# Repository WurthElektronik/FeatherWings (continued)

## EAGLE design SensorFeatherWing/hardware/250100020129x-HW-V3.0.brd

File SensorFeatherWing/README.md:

# Sensor FeatherWing

## Introduction

The Würth Elektronik eiSos [Sensor FeatherWing](https://www.we-online.de/katalog/en/SENSOR_FeatherWing) is a sensor development board fully compatible to the popular [Adafruit](https://www.adafruit.com/) [Feather line](https://www.adafruit.com/feather) of development boards. It consists of the following four sensors:

* [**WSEN-PADS**](https://www.we-online.de/katalog/de/WSEN-PADS) - Absolute pressure sensor [(2511020213301)](https://www.we-online.de/katalog/datasheet/2511020213301.pdf)
* [**WSEN-ITDS**](https://www.we-online.de/katalog/de/WSEN-ITDS) - 3-axis acceleration sensor [(2533020201601)](https://www.we-online.de/katalog/datasheet/2533020201601_valid_from_2020-12-14.pdf)
* [**WSEN-TIDS**](https://www.we-online.de/katalog/de/WSEN-TIDS) - Temperature sensor [(2521020222501)](https://www.we-online.de/katalog/datasheet/2521020222501.pdf)
* [**WSEN-HIDS**](https://www.we-online.de/katalog/de/WSEN-HIDS) - Humidity and temperature sensor [(2525020210002)](https://www.we-online.de/katalog/datasheet/2525020210002.pdf)

All four sensors are connected over the shared I<sup>2</sup>C bus and hence can be connected to any of the Feather microcontroller boards. The available [Arduino](https://www.arduino.cc/) (C/C++) drivers and examples (see [software folder](software)) make it easy to build a prototype to kick-start the application development.

The Sensor FeatherWing also has a [4-pin JST QWIIC®](https://www.sparkfun.com/products/16766) connector on-board. This enables easy connection to SparkFun's [QWIIC® ecosystem](https://www.sparkfun.com/qwiic) of development boards. Additionally, a **6 pin connector** enables the extension of the FeatherWing with a host of [**evaluation boards from Würth Elektronik eiSos**](https://www.we-online.de/catalog/de/wco/wireless-connectivity_1/eval_boards).

This repository contains the [Eagle](https://www.autodesk.com/products/eagle/overview) design files for the Sensor FeatherWing [PCB](hardware) as well as the [software](software) with quick start example.

For more information, please download the [Sensor FeatherWing user manual](docs/SensorFeatherWing.pdf). Feel free to check our [YouTube channel](https://www.youtube.com/user/WuerthElektronik/videos) for video tutorials, hands-ons and webinars relating to our products.

## Hardware

### Description

The Sensor FeatherWing consists of four sensors. This section provides details regarding the key features of these sensors.

### [**WSEN-PADS**](https://www.we-online.de/katalog/de/WSEN-PADS) [(2511020213301)](https://www.we-online.de/katalog/datasheet/2511020213301.pdf)

The WSEN-PADS is a MEMS based piezo-resistive absolute pressure sensor with an integrated ASIC and an embedded temperature sensor. The fully molded holed LGA package and low current consumption makes this sensor suitable for a range of applications including weather stations, barometers, altimeters and indoor navigation.

#### Key features

* Absolute pressure range : 26 to 126 kPa
* Output data rate : 1 to 200 Hz
* Pressure data resolution : 24-bits
* Current consumption : 4 μA
* Programmable pressure threshold and data-ready interrupt

Further details about this sensor can be found under [we-online.de/katalog/en/WSEN-PADS](https://www.we-online.de/katalog/en/WSEN-PADS).

### [**WSEN-ITDS**](https://www.we-online.de/katalog/de/WSEN-ITDS) [(2533020201601)](https://www.we-online.de/katalog/datasheet/2533020201601_valid_from_2020-12-14.pdf)

The WSEN-ITDS sensor is a 14-bit digital ultra-low-power and high-performance three-axis accelerometer with a digital output interface. Capability of detecting events like free fall, tap recognition, wake up, stationary/motion, activity/inactivity and 6D orientation make the sensor suitable for applications like vibration monitoring, tilt measurement, impact detection and many more.

#### Key features

* Selectable full scale : ±2g, ±4g, ±8g, ±16g,
* Bandwidth : 400 Hz
* Output data rate : Up to 1600 Hz
* Noise density : 90 μg / 
* Operating modes : High-performance, Low-power, Normal
* Current consumption : 16 μA (Low-power mode)

Further details about this sensor can be found under [we-online.de/katalog/en/WSEN-ITDS](https://www.we-online.de/katalog/en/WSEN-ITDS).

### [**WSEN-TIDS**](https://www.we-online.de/katalog/de/WSEN-TIDS) [(2521020222501)](https://www.we-online.de/katalog/datasheet/2521020222501.pdf)

The WSEN-TIDS is a high precision silicon-based digital temperature sensor with an integrated ASIC and a digital I<sup>2</sup>C interface. A compact UDFN package and fast thermal response make this sensor ideal for a range of applications like environmental monitoring, HVAC, PCB thermal monitoring, industrial control and many more.

#### Key features

* Temperature range : -40 to 125 °C
* Output data rate : 25 to 200 Hz
* Temperature data resolution : 16-bits
* Current consumption : 1.75 μA
* Programmable temperature threshold interrupt

Further details about this sensor can be found under [we-online.de/katalog/en/WSEN-TIDS](https://www.we-online.de/katalog/en/WSEN-TIDS).

### [**WSEN-HIDS**](https://www.we-online.de/katalog/de/WSEN-HIDS) [(2525020210002)](https://www.we-online.de/katalog/datasheet/2525020210002.pdf)

The WSEN-HIDS is a 16-bit ultra-low power and high-performance humidity sensor with a digital interface. The pre-calibrated sensor in a compact LGA package is suitable for a variety of applications including HVAC systems, white goods, building automation and air conditioning.

#### Key features

* Humidity range : 0 to 100 %rH
* Current consumption : 2.2 μA (In high repeatability mode)
* Resolution : 0.01 %rH
* Response time : 4 s
* Integrated temperature sensor
  
Further details about this sensor can be found under [we-online.de/katalog/en/WSEN-HIDS](https://www.we-online.de/katalog/en/WSEN-HIDS).

### Pinouts

#### Feather Connector
This is the standard set of connectors that is used across the Feather ecosystem. The table below describes the functions of each of the 28 pins as applicable to this FeatherWing.

| Pin number | Pin name | Function |
| ------- | ------- |----------------|
|   1          | <span style="text-decoration:overline">RST</span> | Not connected|
|    2          | 3V3| 3.3 V power supply|
|    3          | AREF| Not connected|
|    4          | GND| Ground|
|    5          | A0| Not connected|
|    6          | A1| Not connected|
|    7          | A2| Not connected|
|    8          | A3| Not connected|
|    9          | A4| Not connected|
|    10         | A5| (Optional) SPI_CE via JP1|
|    11         | SCK| SPI clock|
|    12         | MOSI| SPI MOSI|
|    13         | MISO| SPI MOSI|
|    14         | U0RX| Not connected|
|    15         | U0TX| Not connected|
|    16         | NC| Not connected|

| Pin number | Pin name | Function |
| ------- | ------- |----------------|
|    17         | SDA| I<sup>2</sup>C SDA|
|    18         | SCL|  I<sup>2</sup>C SCL|
|    19         | 5| Not connected|
|    20         | 6| Not connected|
|    21         | 9| Not connected|
|    22         | U1TX| Not connected|
|    23         | U1RX| Not connected|
|    24         | 12| Not connected|
|    25         | 13| Not connected|
|    26         | 5V| 5 V Power supply|
|    27         | EN| Not connected|
|    28         | VBAT| Not connected|

### Layout

#### Connector CON1
Connector CON1 is a 1x5 2.54 mm pin header and provides all the interrupt lines that can be optionally connected to the host. This connector is not mounted.

| Pin number  | Function |
| ------- | ------- |
|     1 |  Not used|
|     2|  Interrupt 1 of the WSEN-ITDS sensor|
|     3 | Interrupt 0 of the WSEN-ITDS sensor |
|     4 | Interrupt of the WSEN-PADS sensor|
|    5 | Interrupt of the WSEN-TIDS sensor| 

#### Connectors CON2 and CON3
CON2 (mounted) and CON3 (not mounted) are 4-pin JST connectors that allow interfacing with [SparkFun's QWIIC®](https://www.sparkfun.com/qwiic) development board ecosystem.
CON3 is not mounted and needs to be soldered on in order to be daisy chain-able. The QWIIC® ecosystem offers a wide range of development boards and accessories for quick prototyping.

| Pin number  | Function |
| ------- | ------- |
|    1 | I<sup>2</sup>C SCL |
|    2|  I<sup>2</sup>C SDA|
|    3 | VCC |
|    4 | GND|

#### Connector CON4
The connector 4 (not mounted) is a 2x3 2.54 mm pitch plug that is compatible with the [Sensor EV-boards](https://www.we-online.de/katalog/de/wco/sensors/evaluation_boards_wsen) from Würth Elektronik using the **SPI** interface.

| Pin number  | Function |
| ------- | ------- |
|    1 | GND|
|    2 | SPI_SCK (Clock) |
|    3|  SPI_MOSI (Master Out Slave In) |
|    4 | SPI_CE (Chip Enable) |
|    5|  SPI_MISO (Master In Slave Out)|
|   6|  VCC|

#### Connector CON5
The connector 5 is a 2x3 2.54 mm pitch plug that is compatible with the [Sensor EV-boards](https://www.we-online.de/katalog/de/wco/sensors/evaluation_boards_wsen) from Würth Elektronik using the **I<sup>2</sup>C** interface.

#### Jumper JP1
This jumper has to be mounted and set when CON4 is used to connect to a sensor using the **SPI** interface.
| Pin connection | Function  | Jumper set (Default) |
| ------- | ------- |----------------|
|    1,2	| SPI_CE(CON4) to GPIOA5 |	No (Not mounted)|

#### Jumper JP2
The standard I<sup>2</sup>C interface requires the SCL and SDA lines to be pulled up with resistors. These jumpers can be removed in cases where the pull-ups already exist on the I<sup>2</sup>C bus.
| Pin connection | Function  | Jumper set (Default) |
| ------- | ------- |----------------|
|    1,2|	Connect  I<sup>2</sup>C SCL line to a 4.7 k<span>&#8486;</span> Pull up resistor|	Yes|
|    3,4|	Connect  I<sup>2</sup>C SDA line to a 4.7 k<span>&#8486;</span> Pull up resistor|	Yes|

### Schematics

### DISCLAIMER:
THE USE OF THE WÜRTH ELEKTRONIK EISOS DESIGN EXAMPLE / REFERENCE DESIGN IS ENTIRELY AT YOUR OWN RISK. IT IS YOUR SOLE RESPONSIBILITY TO IMPLEMENT THE DESIGN EXAMPLE / REFERENCE DESIGN WITH ALL TECHNICAL AND REGULATORY REQUIREMENTS IN YOUR APPLICATION. IT IS ALSO YOUR RESPONSIBILITY TO VERIFY THE FUNCTION AND PERFORMANCE OF YOUR DESIGN IN YOUR OWN PARTICULAR ENGINEERING AND PRODUCT ENVIRONMENT AND YOU ASSUME THE ENTIRE RISK OF DOING SO OR FAILING TO DO SO. THE WÜRTH ELEKTRONIK EISOS DESIGN EXAMPLE / REFERENCE DESIGN IS PROVIDED ON AN "AS IS" OR "AS AVAILABLE" BASIS, WITHOUT ANY WARRANTIES OF ANY KIND AND WÜRTH ELEKTRONIK EISOS DISCLAIMS ANY WARRANTIES EXPRESS OR IMPLIED, INCLUDING WITHOUT LIMITATION THE MERCHANTABILITY OR FITNESS FOR A PARTICULAR PURPOSE, USAGE OR THE NON-INFRINGEMENT OF THIRD PARTIES’ INTELLECTUAL PROPERTY RIGHTS. NO LICENSE IS GRANTED TO ANY INTELLECTUAL PROPERTY RIGHT BY WÜRTH ELEKTRONIK EISOS OR ANY THIRD PARY. UNDER NO CIRCUMSTANCES SHALL WÜRTH ELEKTRONIK EISOS BE LIABLE FOR DAMAGES INCURRED BY REASON OF OTHER SERVICES OR PRODUCTS RECEIVED THROUGH OR ADVERTISED IN CONNECTION WITH THE WÜRTH ELEKTRONIK EISOS SITE OR THE WÜRTH ELEKTRONIK EISOS DESIGN EXAMPLE / REFERENCE DESIGN. THE WÜRTH ELEKTRONIK EISOS DESIGN EXAMPLE / REFERENCE DESIGN IS SUBJECT TO CHANGE WITHOUT NOTICE.

## Software

Sensor FeatherWing **software examples** can be found in the [software folder](software).

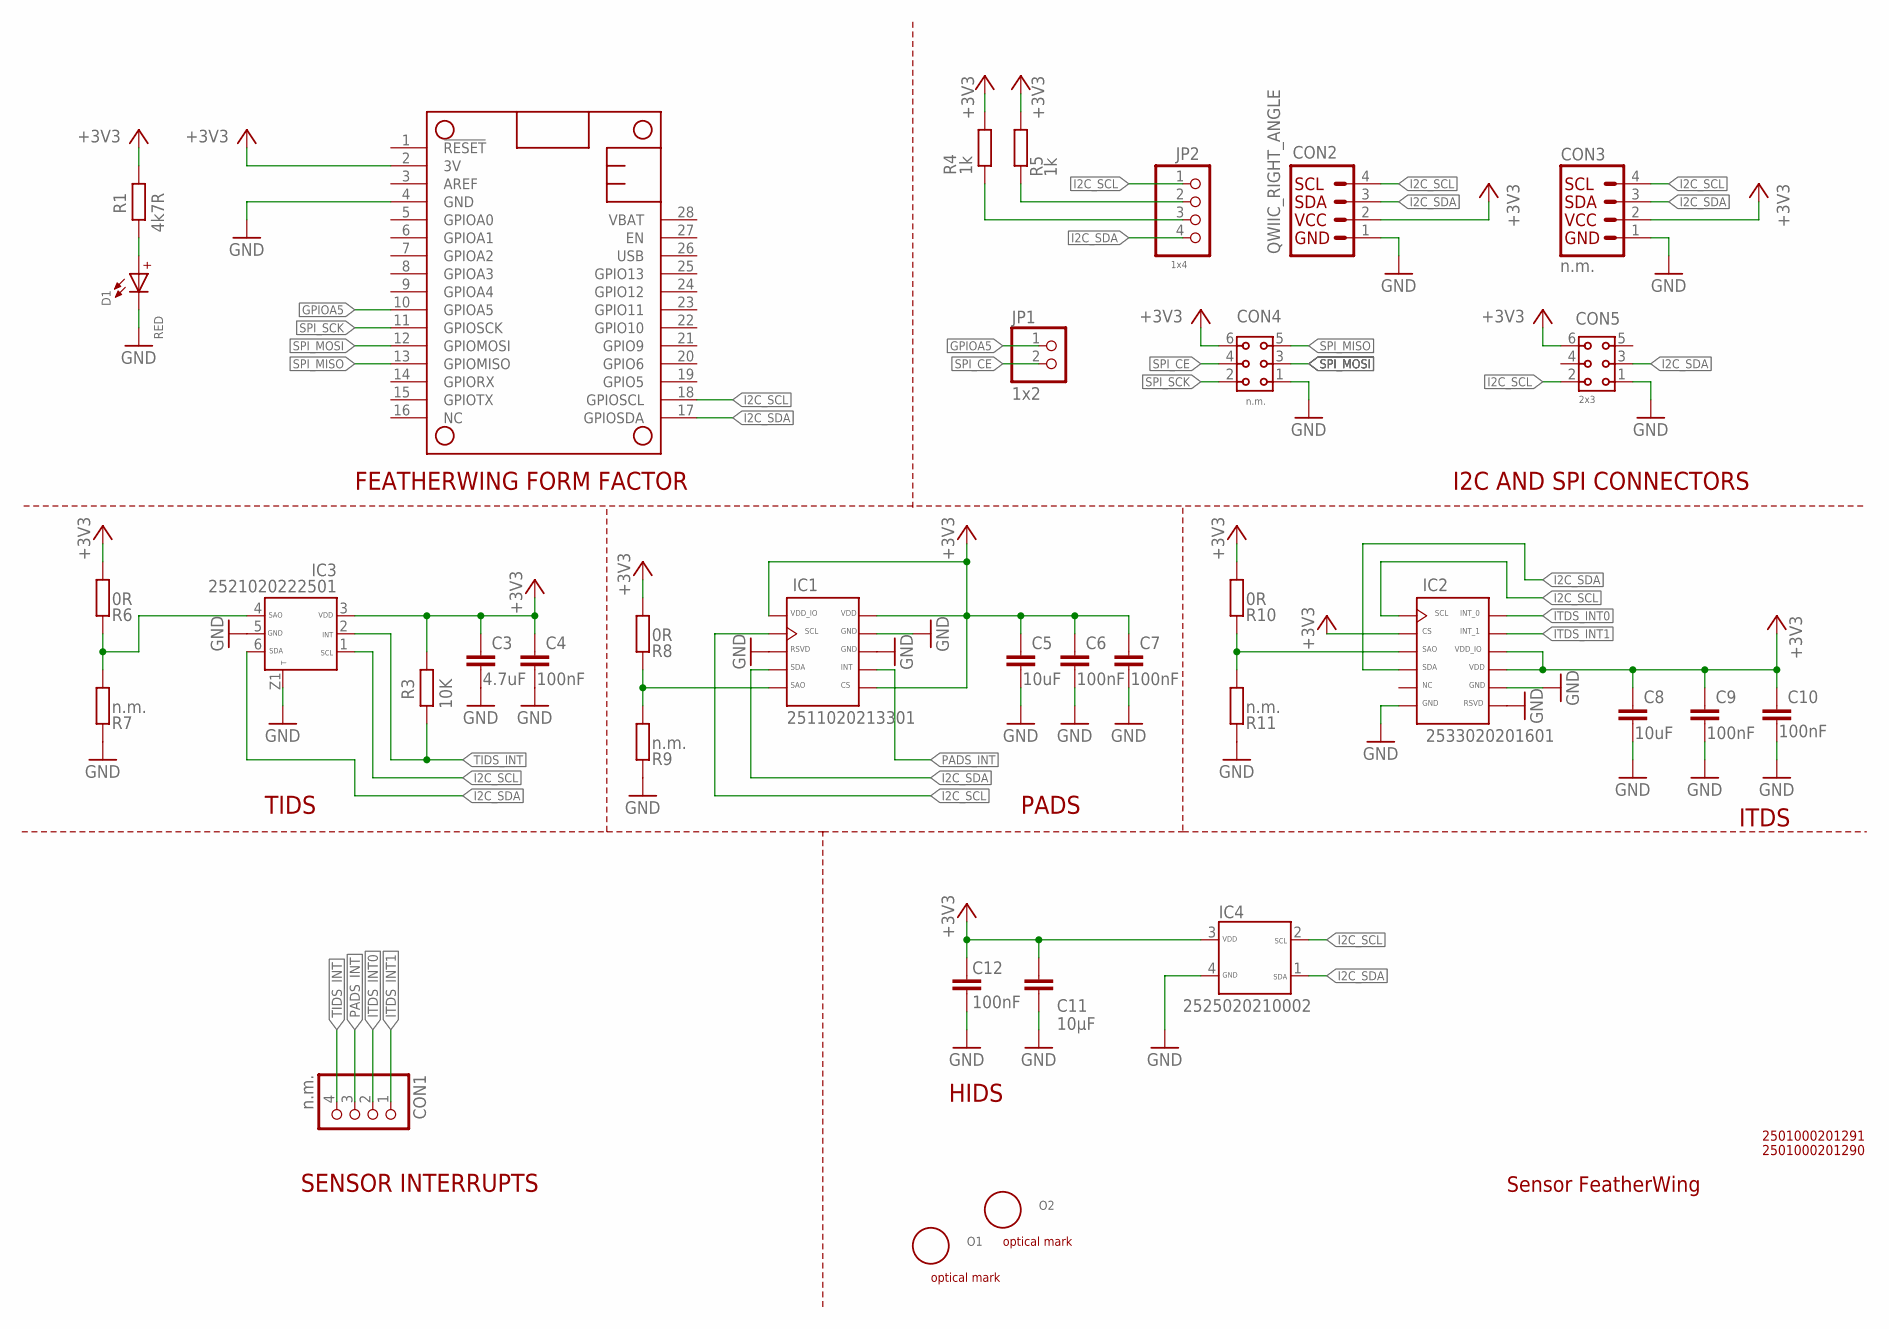
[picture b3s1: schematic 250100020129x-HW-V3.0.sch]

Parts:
C3: 4.7uF; C0402_IPC
C4, C6, C7, C9, C10, C12: 100nF; C0402_IPC
C5, C8: 10uF; C0402_IPC
C11: 10µF; C0402_IPC
CON1: n.m.; 1X04/R
CON2: QWIIC_RIGHT_ANGLE; JST04_1MM_RA
CON3: n.m.; JST04_1MM_RA
CON4: n.m.; 613006243121
CON5: 2x3; 613006243121
D1: RED; WL-SMSW_1204_A
IC1: 2511020213301; WSEN-PADS_2511020213301
IC2: 2533020201601; WSEN-ITDS_2533020201601
IC3: 2521020222501; WSEN-TIDS_2521020222501
IC4: 2525020210002; WSEN-HIDS_2525020210002
JP1: 1x2; 1X02/R
JP2: 1x4; 1X04/R
MS1: FEATHERWING
O1, O2: OPT_MARKE; OPTISCHE_MARKE
R1: 4k7R; R0402_IPC
R3: 10K; R0402_IPC
R4, R5: 1k; R0402_IPC
R6, R8, R10: 0R; R0402_IPC
R7, R9, R11: n.m.; R0402_IPC

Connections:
+3V3: C3.1, C4.1, C5.1, C6.1, C7.1, C8.1, C9.1, C10.1, C11.2, C12.2, CON2.2, CON3.2, CON4.6, CON5.6, IC1.1 (VDD_IO), IC1.6 (CS), IC1.10 (VDD), IC2.2 (CS), IC2.9 (VDD), IC2.10 (VDD_IO), IC3.3 (VDD), IC4.3 (VDD), MS1.2 (3V), R1.2, R3.2, R4.2, R5.2, R6.2, R8.2, R10.2
GND: C3.2, C4.2, C5.2, C6.2, C7.2, C8.2, C9.2, C10.2, C11.1, C12.1, CON2.1, CON3.1, CON4.1, CON5.1, D1.1 (-), IC1.3 (RSVD), IC1.8 (GND), IC1.9 (GND), IC2.6 (GND), IC2.7 (RSVD), IC2.8 (GND), IC3.5 (GND), IC3.Z1, IC4.4 (GND), MS1.4 (GND), R7.1, R9.1, R11.1
GPIOA5: JP1.1, MS1.10 (GPIOA5)
I2C_SCL: CON2.4, CON3.4, CON5.2, IC1.2 (SCL), IC2.1 (SCL), IC3.1 (SCL), IC4.2 (SCL), JP2.1, MS1.18 (GPIOSCL)
I2C_SDA: CON2.3, CON3.3, CON5.3, IC1.4 (SDA), IC2.4 (SDA), IC3.6 (SDA), IC4.1 (SDA), JP2.4, MS1.17 (GPIOSDA)
ITDS_INT0: CON1.2, IC2.12 (INT_0)
ITDS_INT1: CON1.1, IC2.11 (INT_1)
unnamed: D1.2 (+), R1.1
unnamed: JP2.2, R5.1
unnamed: JP2.3, R4.1
unnamed: IC3.4 (SAO), R6.1, R7.2
unnamed: IC2.3 (SAO), R10.1, R11.2
unnamed: IC1.5 (SAO), R8.1, R9.2
PADS_INT: CON1.3, IC1.7 (INT)
SPI_CE: CON4.4, JP1.2
SPI_MISO: CON4.5, MS1.13 (GPIOMISO)
SPI_MOSI: CON4.3, MS1.12 (GPIOMOSI)
SPI_SCK: CON4.2, MS1.11 (GPIOSCK)
TIDS_INT: CON1.4, IC3.2 (INT), R3.1

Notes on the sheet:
Sensor FeatherWing
TIDS
PADS
ITDS
I2C AND SPI CONNECTORS
FEATHERWING FORM FACTOR
2501000201291
2501000201290
HIDS
SENSOR INTERRUPTS

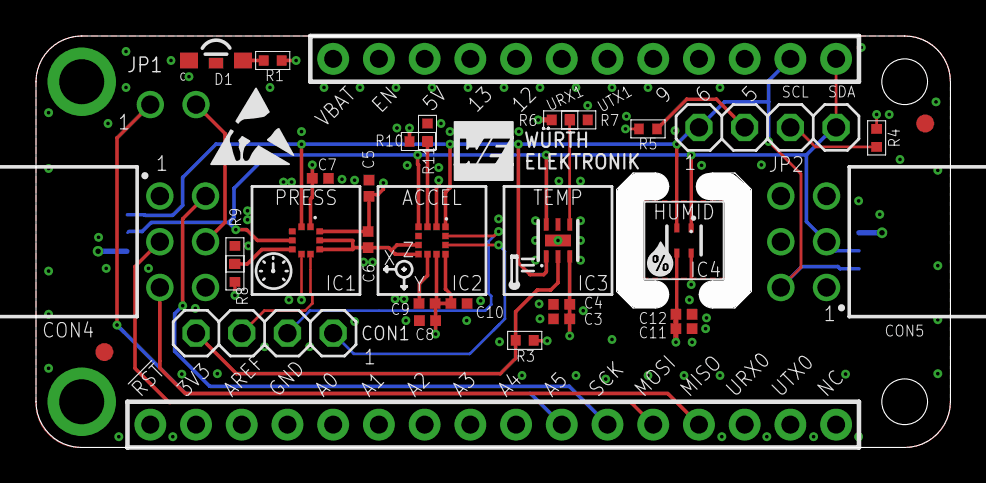
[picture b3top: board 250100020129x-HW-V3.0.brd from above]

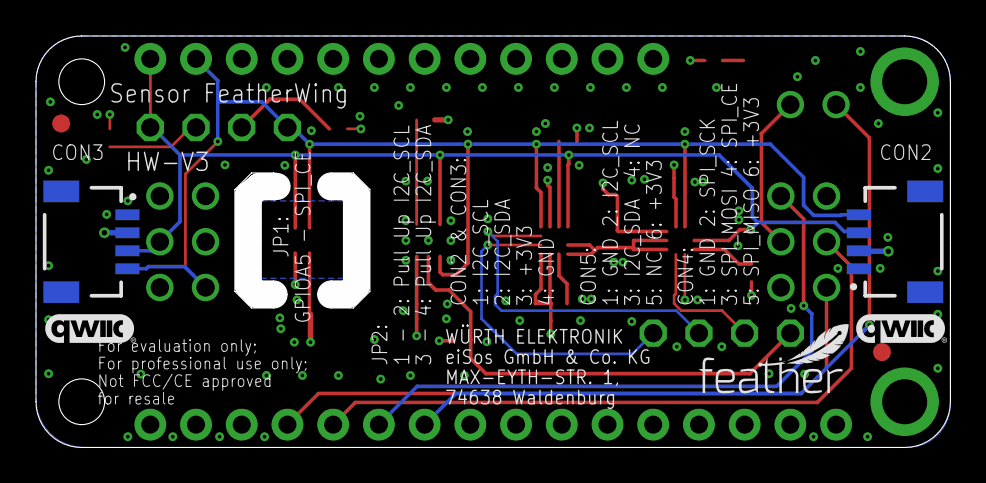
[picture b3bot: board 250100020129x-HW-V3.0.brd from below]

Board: 4 copper layers, 50.8 x 22.9 mm, 43 parts (5 on the bottom side), 19 nets.

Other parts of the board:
U$1, U$9: QWICC_5MM
U$2: WE-NEU-3.5MM
U$3: HIDS_2MM
U$4: ESD_5MM
U$6: FEATHER_8MM
U$7: TIDS_2MM
U$8: PADS_2.2MM

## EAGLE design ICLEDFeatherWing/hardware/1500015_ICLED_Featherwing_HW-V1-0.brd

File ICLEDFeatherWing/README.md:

# ICLED

## Introduction

The [ICLED](https://www.we-online.com/en/components/products/WL-ICLED) was designed with rapid prototyping in mind. Being fully compatible with the Adafruit ecosystem, this FeatherWing gives the user the flexibility to choose the preferred host microcontroller. The inherent modularity of the ecosystem allows the FeatherWing to be easily integrated into any project.

The ICLEDFeatherWing contains 105 IC LEDs ([**1312020030000**](https://www.we-online.com/en/components/products/WL-ICLED?sq=1312020030000#1312020030000)) in a 7x15 display shape with a pitch of 2.38 mm. It can be controlled by any adafruit feather micro-controller board and
is powered by USB-C (5 V@3 A) or LiPoly battery. The display is controlled by only 1 pin while a second GPIO-pin is used to trigger an interrupt by pushing the ”Prog”-button on featherwing. Internal Level-shifter makes logic-levels lower than 3.3 V possible and with that usage of other micro-controllers than adafruit feathers.

## Hardware description

This sections contains a detailed description of the hardware features of the ICLEDFeatherWing.

### Connectors

This section explains all connectors of the ICLEDFeatherWing.

| Pin header | Function | WE-article Number |
| ------- | ------- |----------------|
| Feather connector| Connection to Feather M0 or other FeatherWings | [**61301211121**](https://www.we-online.com/en/components/products/PHD_2_54_THT_PIN_HEADER_6130XX11121?sq=61301211121#6130121112) / [**61301611121**](https://www.we-online.com/en/components/products/PHD_2_54_THT_PIN_HEADER_6130XX11121?sq=61301611121#61301611121) |
| CON1 | USB-C connector for VDD bus supply | [**629722000214**](https://www.we-online.com/de/components/products/WR-COM_USB_20_TYPE_C_RECEPTACLE_HORIZONTAL_SMT?sq=629722000214#629722000214) |

### Feather connector
This is the standard set of connectors that is used across the Feather ecosystem. The table below describes the functions of each of the 28 pins as applicable to this FeatherWing.
| Pin number | Pin name | Function |
| ------- | ------- |----------------|
|   1          | <span style="text-decoration:overline">RST</span> | <span style="text-decoration:overline">RST</span>|
|    2          | 3V3| 3.3 V power supply|
|    3          | AREF| Not connected|
|    4          | GND| Ground|
|    5          | A0| Not connected|
|    6          | A1| Not connected|
|    7          | A2| Not connected|
|    8          | A3| Not connected|
|    9          | A4| Not connected|
|    10         | A5| (Optional) SPI_CE via JP1|
|    11         | SCK| Not Connected|
|    12         | MOSI| (Optional) DI via R10|
|    13         | MISO| Not Connected|
|    14         | U0RX| Not connected|
|    15         | U0TX| Not connected|
|    16         | NC| Not connected|
|    17         | SDA| Not Connected|
|    18         | SCL|  Not Connected|
|    19         | 5| S2|
|    20         | 6| DI via R9|
|    21         | 9| Not connected|
|    22         | U1TX| Not connected|
|    23         | U1RX| Not connected|
|    24         | 12|(Optional) DI via R4 |
|    25         | 13| Not connected|
|    26         | 5V| Optional) USB power via R8|
|    27         | EN| Not connected|
|    28         | VBA| Battery Power via D2|

### CON1

Connector CON1 is a USB-C connector designed for connecting to a power source (e.g. PC) using a standard USB-C cable. It is strongly advised against using a USB-Type-A to USBType-C adapter. The 5.1 kΩ resistors placed on the CC-lines will handle out up to 3 A from
power source. However, the actual maximum current delivered will depend on what the power source can safely provide.

| CON1  | Function |
| ------- | ------- |
| - |USB-C connector for VDD bus supply |

### JPI
Connector JP1 is an optional standard 2.54 mm pinheader, which is not mounted by default.It can be used to combine multiple ICLEDFeatherWings or with other ICLEDscreens. JP1 is
directly connected to the DOUT Pin of ICLED105.

| JP1  | Function |
| ------- | ------- |
| 1 |Data Out of last IC LED|

### JP2
Connector JP2 is an optional standard 2.54 mm pinheader, which is not mounted by default.It can be used to combine multiple ICLEDFeatherWings or with other ICLEDscreens. JP2 is
connected to DIN Pin of ICLED1 via U1 and R5 or optional directly to DIN of ICLED1 via R3.

| JP2  | Function |
| ------- | ------- |
| 1 |Data In of Level-Shifter (U1)|

### DIN pin
The Data In (DIN) Pin is Pin 20 (GPIO 6) by default. It can be changed by removing R9 from
board. If a 0 Ω resistor is placed for R4, pin 24 (GPIO 12) is the new DIN pin. By soldering a
0 Ω resistor for R10 it is also possible to use pin 12 (MOSI) for data input. Instead of soldering
a 0 Ω resistor, it is also an option to short-circuit pads with solder. If needed, JP2 can be used
as data input pin.
DIN is connected to level-shifter (U1) via R5 by default. If R5 is removed and a 0Ω resistor is
placed for R3, DIN is directly connected to DIN pin of LED1. This is highly recommended, if
input logic level is higher than 3.6 V, to avoid damaging U1. Please remind, that the maximum
input voltage level is 5.5 V for ICLEDFeatherWing.
Input reference level for U1 is 3V3. By supplying 3V3 pin with input logic voltage, any logic level
between 1.65 V and 3.6 V can be shifted to 5 V.

## Push buttons

### S1
This push button is connected to the /RESET pin of the Feather connector. Pressing this button
resets m0.
### S2
This push button is connected to Pin 5 of the Feather connector. Pressing this button pulls pin
5 to signal low. It is recommended to set this pin as an input with internal pull-up by software.
It is recommended to use this pin for interrupt functions for example to change displayed data.

# DISCLAIMER

THE USE OF THE WÜRTH ELEKTRONIK EISOS DESIGN EXAMPLE / REFERENCE DESIGN IS ENTIRELY AT YOUR OWN RISK. IT IS YOUR SOLE RESPONSIBILITY TO IMPLEMENT THE DESIGN EXAMPLE / REFERENCE DESIGN WITH ALL TECHNICAL AND REGULATORY REQUIREMENTS IN YOUR APPLICATION. IT IS ALSO YOUR RESPONSIBILITY TO VERIFY THE FUNCTION AND PERFORMANCE OF YOUR DESIGN IN YOUR OWN PARTICULAR ENGINEERING AND PRODUCT ENVIRONMENT AND YOU ASSUME THE ENTIRE RISK OF DOING SO OR FAILING TO DO SO. THE WÜRTH ELEKTRONIK EISOS DESIGN EXAMPLE / REFERENCE DESIGN IS PROVIDED ON AN "AS IS" OR "AS AVAILABLE" BASIS, WITHOUT ANY WARRANTIES OF ANY KIND AND WÜRTH ELEKTRONIK EISOS DISCLAIMS ANY WARRANTIES EXPRESS OR IMPLIED, INCLUDING WITHOUT LIMITATION THE MERCHANTABILITY OR FITNESS FOR A PARTICULAR PURPOSE, USAGE OR THE NON-INFRINGEMENT OF THIRD PARTIES’ INTELLECTUAL PROPERTY RIGHTS. NO LICENSE IS GRANTED TO ANY INTELLECTUAL PROPERTY RIGHT BY WÜRTH ELEKTRONIK EISOS OR ANY THIRD PARY. UNDER NO CIRCUMSTANCES SHALL WÜRTH ELEKTRONIK EISOS BE LIABLE FOR DAMAGES INCURRED BY REASON OF OTHER SERVICES OR PRODUCTS RECEIVED THROUGH OR ADVERTISED IN CONNECTION WITH THE WÜRTH ELEKTRONIK EISOS SITE OR THE WÜRTH ELEKTRONIK EISOS DESIGN EXAMPLE / REFERENCE DESIGN. THE WÜRTH ELEKTRONIK EISOS DESIGN EXAMPLE / REFERENCE DESIGN IS SUBJECT TO CHANGE WITHOUT NOTICE.

## Software

IC LED FeatherWing software examples can be found in the [software folder](software).

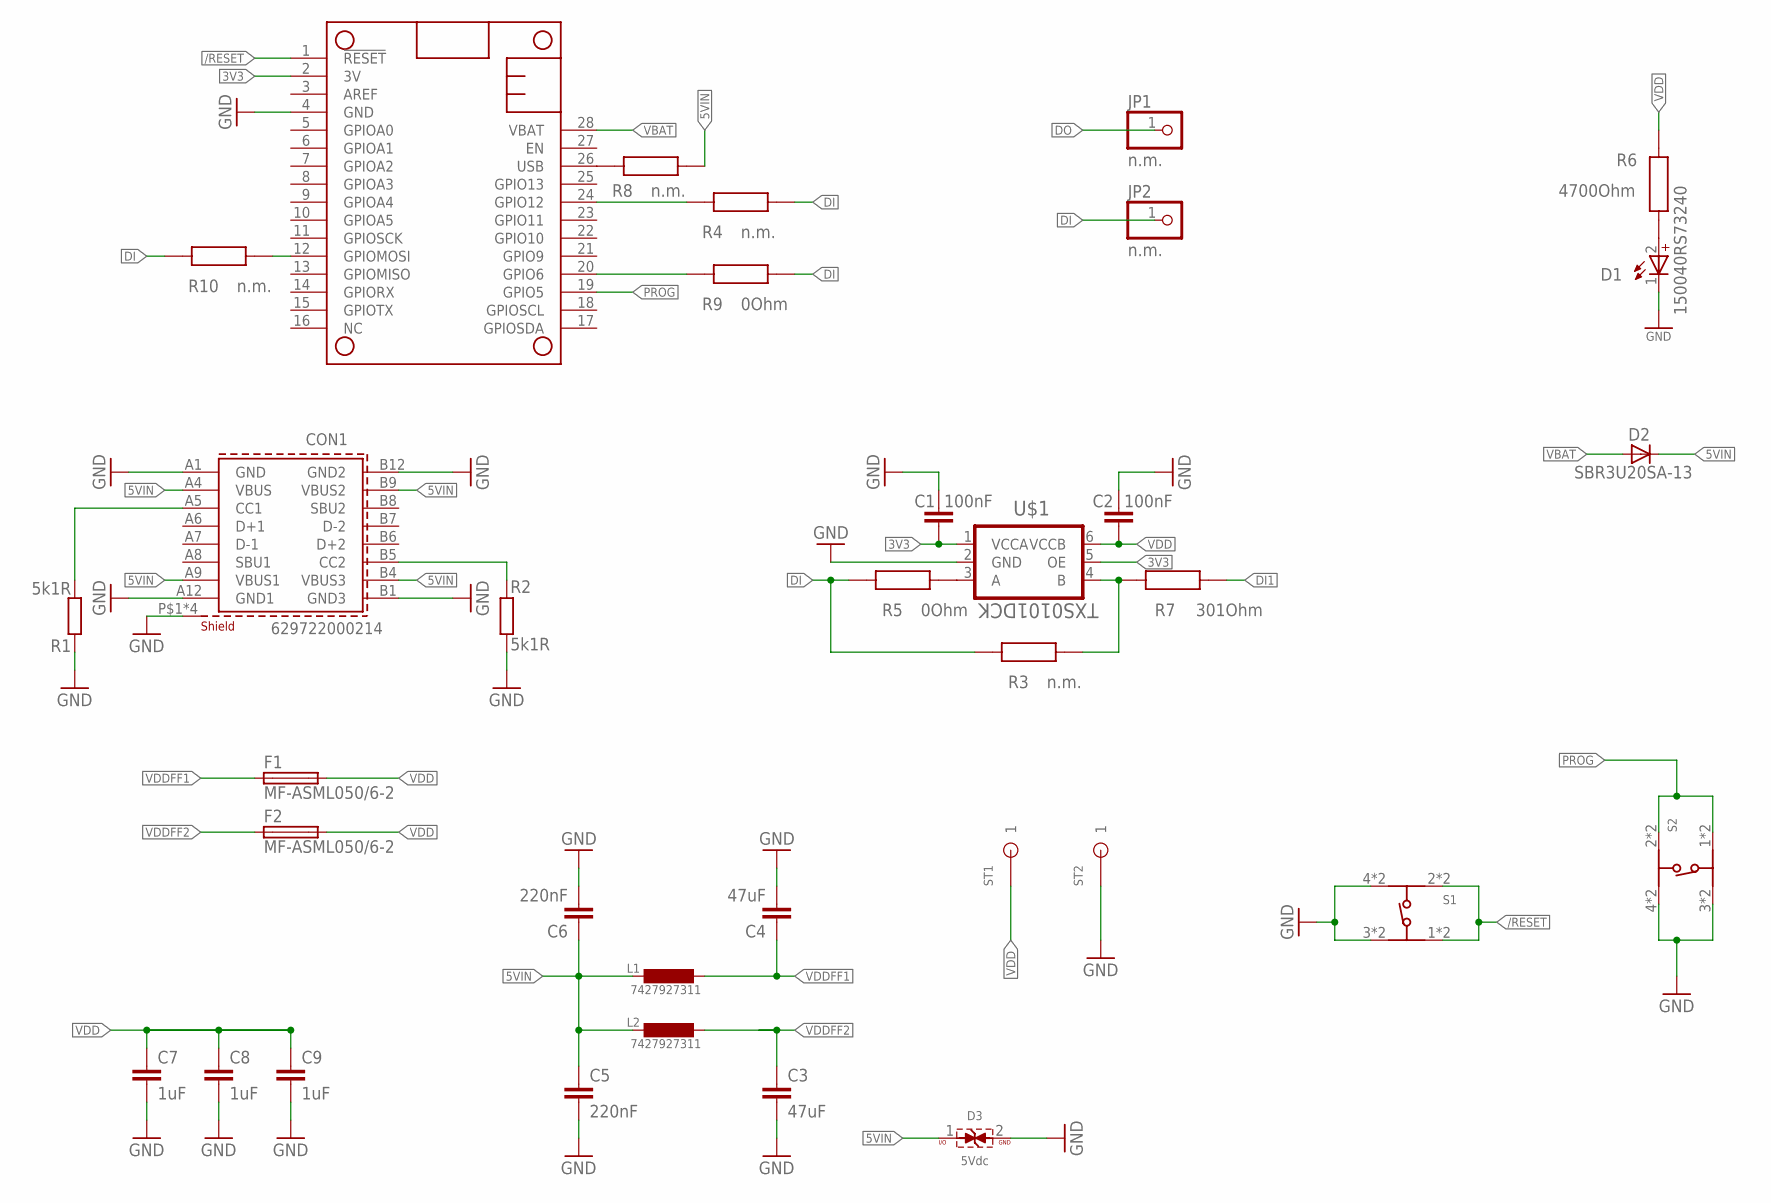
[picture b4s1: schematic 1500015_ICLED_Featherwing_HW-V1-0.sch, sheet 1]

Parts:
C1, C2: 100nF; C0402_IPC
C3, C4: 47uF; C0805
C5, C6: 220nF; C0603_IPC
C7, C8, C9: 1uF; C0402_IPC
CON1: 629722000214
D1: 150040RS73240; WL-SMCC_0402
D2: SBR3U20SA-13; SBR3U20SA
D3: 5Vdc; WE-TVS_DFN1610-2L
F1, F2: MF-ASML050/6-2; 0402
JP1, JP2: n.m.; 1X01/R
L1, L2: 7427927311; L0402_WE_FERRIT
MS1: FEATHERWING
R1, R2: 5k1R; R0402_IPC
R3, R10: n.m.; WRIS-RSKS_0603_WAVE
R4, R8: n.m.; WRIS-RSKS_0402
R5, R9: 0Ohm; WRIS-RSKS_0603_WAVE
R6: 4700Ohm; WRIS-RSKS_0402
R7: 301Ohm; WRIS-RSKS_0402
S1, S2: 434331013822; 434331013822_ICLEDFW_ANGEPASST
ST1, ST2: 1_5X1MM
U$1: TXS0101DCK; SC70

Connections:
3V3: C1.2, MS1.2 (3V), U$1.1 (VCCA), U$1.5 (OE)
5VIN: C5.1, C6.1, CON1.A4 (VBUS), CON1.A9 (VBUS1), CON1.B4 (VBUS3), CON1.B9 (VBUS2), D2.K (C), D3.1 (I/O), L1.P$2 (2), L2.P$2 (2), R8.2
/RESET: MS1.1 (!RESET), S1.1, S1.2, S1.7 (1), S1.8 (2)
DI: JP2.1, R3.2, R4.2, R5.2, R9.2, R10.2
DI1: R7.2; also elsewhere on the board
DILS: R3.1, R7.1, U$1.4 (B)
DO: JP1.1; also elsewhere on the board
GND: C1.1, C2.1, C3.P$2 (2), C4.P$2 (2), C5.2, C6.2, C7.2, C8.2, C9.2, CON1.A1 (GND), CON1.A12 (GND1), CON1.B1 (GND3), CON1.B12 (GND2), CON1.P$1 (SHIELD), CON1.P$2 (SHIELD), CON1.P$3 (SHIELD), CON1.P$4 (SHIELD), D1.1 (-), D3.2 (GND), MS1.4 (GND), R1.1, R2.2, S1.3, S1.4, S1.5 (4), S1.6 (3), S2.3, S2.4, S2.5 (4), S2.6 (3), ST2.1, U$1.2 (GND); also elsewhere on the board
GPIO6: MS1.20 (GPIO6), R9.1
GPIO12: MS1.24 (GPIO12), R4.1
MOSI: MS1.12 (GPIOMOSI), R10.1
unnamed: CON1.A5 (CC1), R1.2
unnamed: CON1.B5 (CC2), R2.1
unnamed: R5.1, U$1.3 (A)
unnamed: D1.2 (+), R6.1
PROG: MS1.19 (GPIO5), S2.1, S2.2, S2.7 (1), S2.8 (2)
USB: MS1.26 (USB), R8.1
VBAT: D2.A, MS1.28 (VBAT)
VDD: C2.2, C7.1, C8.1, C9.1, F1.2, F2.2, R6.2, ST1.1, U$1.6 (VCCB); also elsewhere on the board
VDDFF1: C4.P$1 (1), F1.1, L1.P$1 (1)
VDDFF2: C3.P$1 (1), F2.1, L2.P$1 (1)

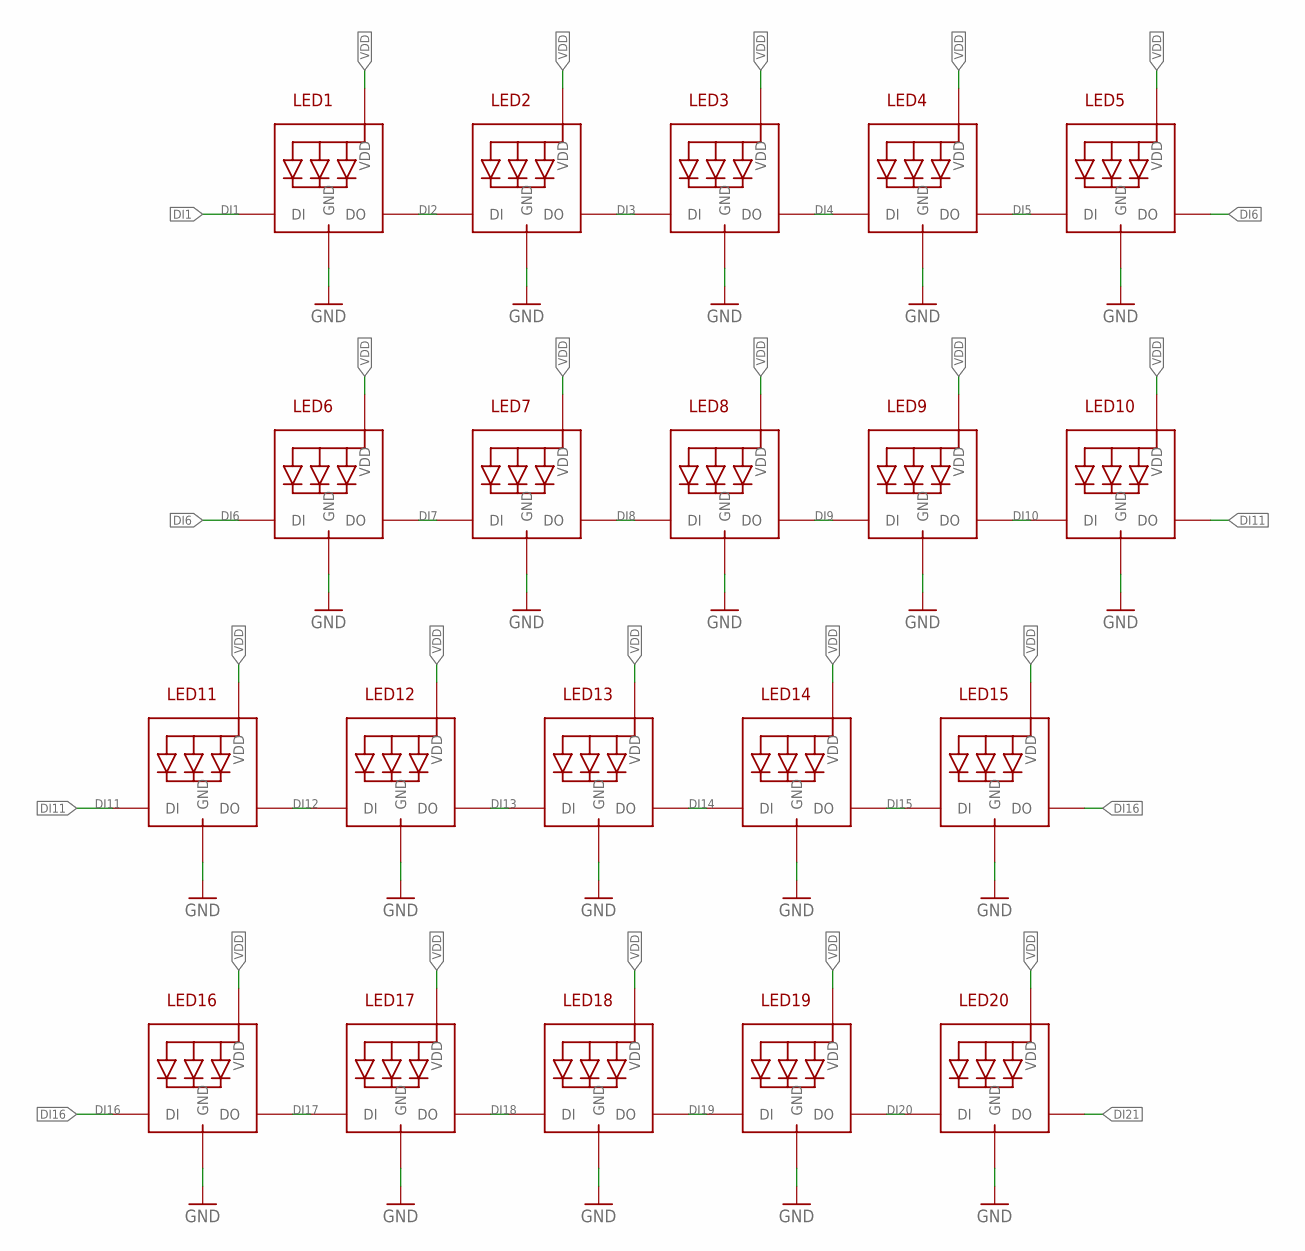
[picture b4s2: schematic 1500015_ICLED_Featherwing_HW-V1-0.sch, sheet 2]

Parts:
LED1, LED2, LED3, LED4, LED5, LED6, LED7, LED8, LED9, LED10, LED11, LED12, LED13, LED14, LED15, LED16, LED17, LED18, LED19, LED20: 1312020030000; 1312020030000_FWANGEPASST

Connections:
DI1: LED1.3-DIN (DI); also elsewhere on the board
DI2: LED1.1-DOUT (DO), LED2.3-DIN (DI)
DI3: LED2.1-DOUT (DO), LED3.3-DIN (DI)
DI4: LED3.1-DOUT (DO), LED4.3-DIN (DI)
DI5: LED4.1-DOUT (DO), LED5.3-DIN (DI)
DI6: LED5.1-DOUT (DO), LED6.3-DIN (DI)
DI7: LED6.1-DOUT (DO), LED7.3-DIN (DI)
DI8: LED7.1-DOUT (DO), LED8.3-DIN (DI)
DI9: LED8.1-DOUT (DO), LED9.3-DIN (DI)
DI10: LED9.1-DOUT (DO), LED10.3-DIN (DI)
DI11: LED10.1-DOUT (DO), LED11.3-DIN (DI)
DI12: LED11.1-DOUT (DO), LED12.3-DIN (DI)
DI13: LED12.1-DOUT (DO), LED13.3-DIN (DI)
DI14: LED13.1-DOUT (DO), LED14.3-DIN (DI)
DI15: LED14.1-DOUT (DO), LED15.3-DIN (DI)
DI16: LED15.1-DOUT (DO), LED16.3-DIN (DI)
DI17: LED16.1-DOUT (DO), LED17.3-DIN (DI)
DI18: LED17.1-DOUT (DO), LED18.3-DIN (DI)
DI19: LED18.1-DOUT (DO), LED19.3-DIN (DI)
DI20: LED19.1-DOUT (DO), LED20.3-DIN (DI)
DI21: LED20.1-DOUT (DO); also elsewhere on the board
GND: LED1.4-GND (GND), LED2.4-GND (GND), LED3.4-GND (GND), LED4.4-GND (GND), LED5.4-GND (GND), LED6.4-GND (GND), LED7.4-GND (GND), LED8.4-GND (GND), LED9.4-GND (GND), LED10.4-GND (GND), LED11.4-GND (GND), LED12.4-GND (GND), LED13.4-GND (GND), LED14.4-GND (GND), LED15.4-GND (GND), LED16.4-GND (GND), LED17.4-GND (GND), LED18.4-GND (GND), LED19.4-GND (GND), LED20.4-GND (GND); also elsewhere on the board
VDD: LED1.2-VDD (VDD), LED2.2-VDD (VDD), LED3.2-VDD (VDD), LED4.2-VDD (VDD), LED5.2-VDD (VDD), LED6.2-VDD (VDD), LED7.2-VDD (VDD), LED8.2-VDD (VDD), LED9.2-VDD (VDD), LED10.2-VDD (VDD), LED11.2-VDD (VDD), LED12.2-VDD (VDD), LED13.2-VDD (VDD), LED14.2-VDD (VDD), LED15.2-VDD (VDD), LED16.2-VDD (VDD), LED17.2-VDD (VDD), LED18.2-VDD (VDD), LED19.2-VDD (VDD), LED20.2-VDD (VDD); also elsewhere on the board

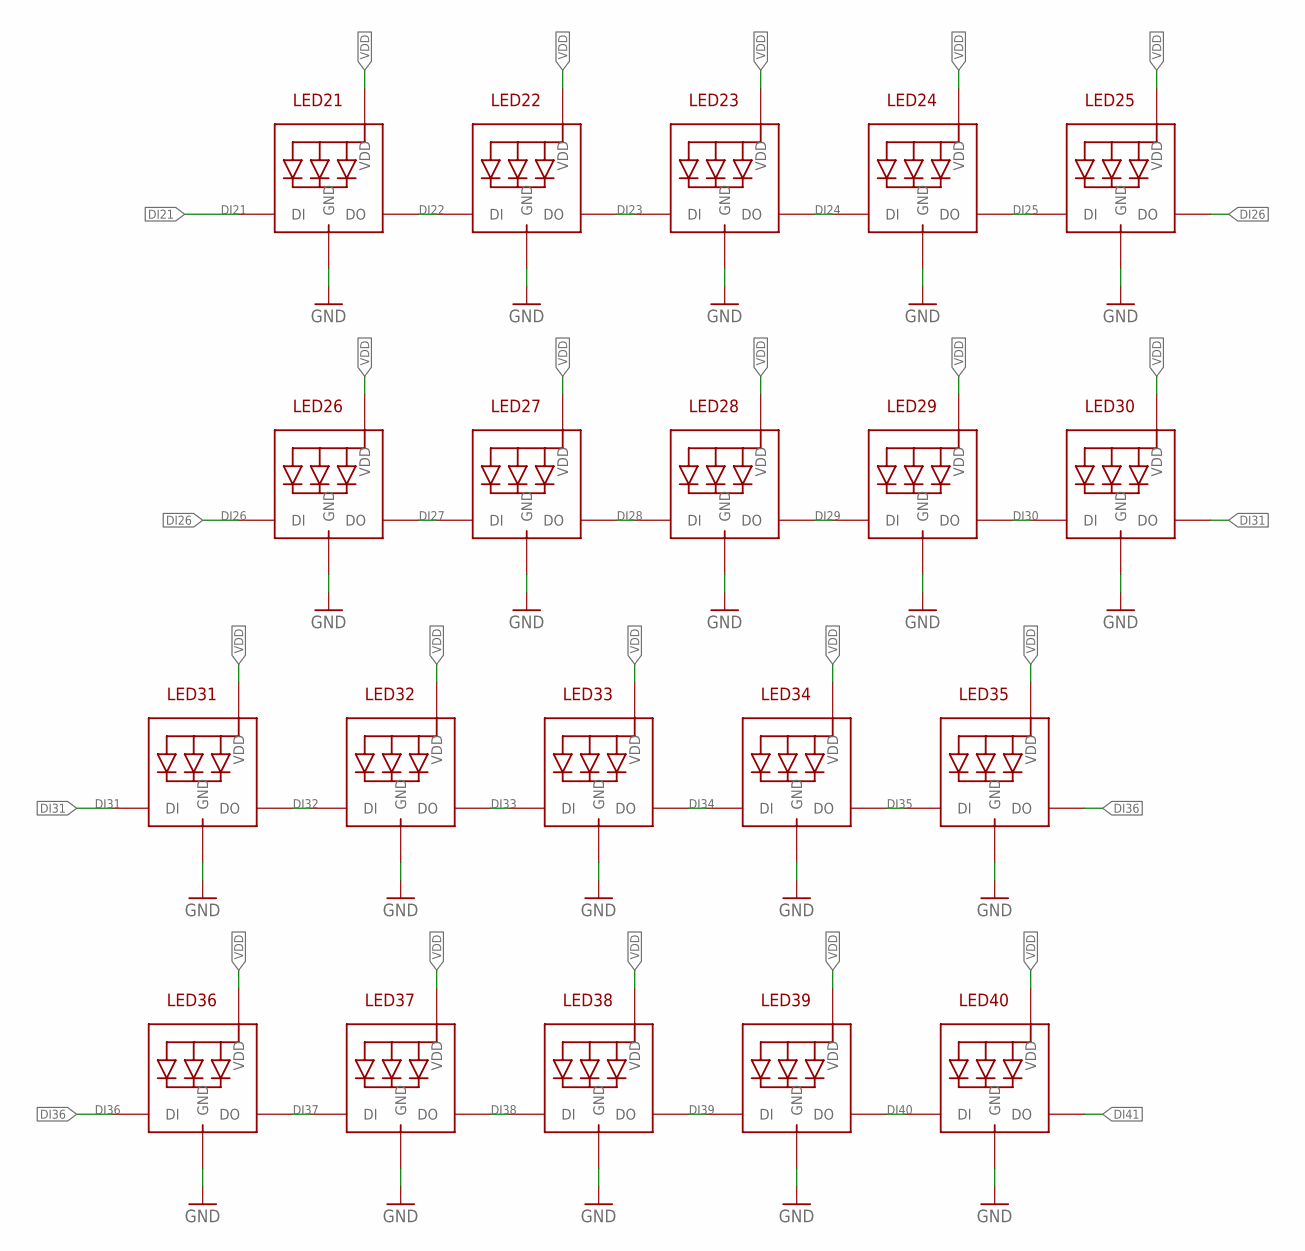
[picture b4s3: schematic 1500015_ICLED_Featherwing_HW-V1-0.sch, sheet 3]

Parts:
LED21, LED22, LED23, LED24, LED25, LED26, LED27, LED28, LED29, LED30, LED31, LED32, LED33, LED34, LED35, LED36, LED37, LED38, LED39, LED40: 1312020030000; 1312020030000_FWANGEPASST

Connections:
DI21: LED21.3-DIN (DI); also elsewhere on the board
DI22: LED21.1-DOUT (DO), LED22.3-DIN (DI)
DI23: LED22.1-DOUT (DO), LED23.3-DIN (DI)
DI24: LED23.1-DOUT (DO), LED24.3-DIN (DI)
DI25: LED24.1-DOUT (DO), LED25.3-DIN (DI)
DI26: LED25.1-DOUT (DO), LED26.3-DIN (DI)
DI27: LED26.1-DOUT (DO), LED27.3-DIN (DI)
DI28: LED27.1-DOUT (DO), LED28.3-DIN (DI)
DI29: LED28.1-DOUT (DO), LED29.3-DIN (DI)
DI30: LED29.1-DOUT (DO), LED30.3-DIN (DI)
DI31: LED30.1-DOUT (DO), LED31.3-DIN (DI)
DI32: LED31.1-DOUT (DO), LED32.3-DIN (DI)
DI33: LED32.1-DOUT (DO), LED33.3-DIN (DI)
DI34: LED33.1-DOUT (DO), LED34.3-DIN (DI)
DI35: LED34.1-DOUT (DO), LED35.3-DIN (DI)
DI36: LED35.1-DOUT (DO), LED36.3-DIN (DI)
DI37: LED36.1-DOUT (DO), LED37.3-DIN (DI)
DI38: LED37.1-DOUT (DO), LED38.3-DIN (DI)
DI39: LED38.1-DOUT (DO), LED39.3-DIN (DI)
DI40: LED39.1-DOUT (DO), LED40.3-DIN (DI)
DI41: LED40.1-DOUT (DO); also elsewhere on the board
GND: LED21.4-GND (GND), LED22.4-GND (GND), LED23.4-GND (GND), LED24.4-GND (GND), LED25.4-GND (GND), LED26.4-GND (GND), LED27.4-GND (GND), LED28.4-GND (GND), LED29.4-GND (GND), LED30.4-GND (GND), LED31.4-GND (GND), LED32.4-GND (GND), LED33.4-GND (GND), LED34.4-GND (GND), LED35.4-GND (GND), LED36.4-GND (GND), LED37.4-GND (GND), LED38.4-GND (GND), LED39.4-GND (GND), LED40.4-GND (GND); also elsewhere on the board
VDD: LED21.2-VDD (VDD), LED22.2-VDD (VDD), LED23.2-VDD (VDD), LED24.2-VDD (VDD), LED25.2-VDD (VDD), LED26.2-VDD (VDD), LED27.2-VDD (VDD), LED28.2-VDD (VDD), LED29.2-VDD (VDD), LED30.2-VDD (VDD), LED31.2-VDD (VDD), LED32.2-VDD (VDD), LED33.2-VDD (VDD), LED34.2-VDD (VDD), LED35.2-VDD (VDD), LED36.2-VDD (VDD), LED37.2-VDD (VDD), LED38.2-VDD (VDD), LED39.2-VDD (VDD), LED40.2-VDD (VDD); also elsewhere on the board

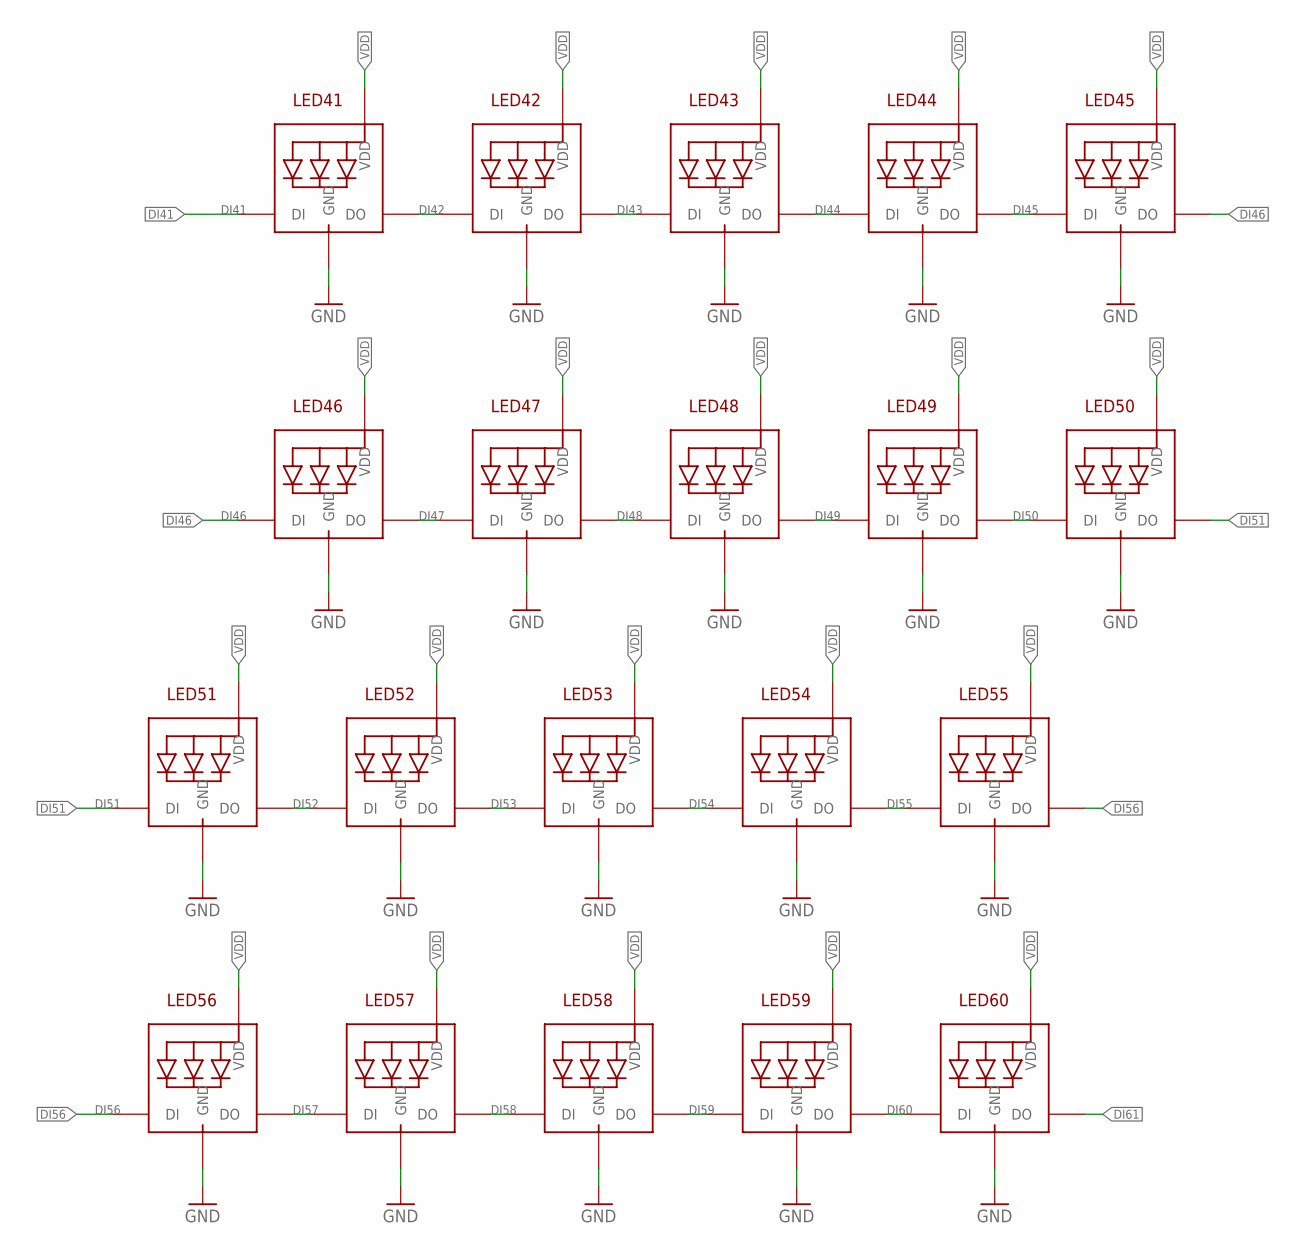
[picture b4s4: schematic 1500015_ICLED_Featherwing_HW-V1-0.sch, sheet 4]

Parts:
LED41, LED42, LED43, LED44, LED45, LED46, LED47, LED48, LED49, LED50, LED51, LED52, LED53, LED54, LED55, LED56, LED57, LED58, LED59, LED60: 1312020030000; 1312020030000_FWANGEPASST

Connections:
DI41: LED41.3-DIN (DI); also elsewhere on the board
DI42: LED41.1-DOUT (DO), LED42.3-DIN (DI)
DI43: LED42.1-DOUT (DO), LED43.3-DIN (DI)
DI44: LED43.1-DOUT (DO), LED44.3-DIN (DI)
DI45: LED44.1-DOUT (DO), LED45.3-DIN (DI)
DI46: LED45.1-DOUT (DO), LED46.3-DIN (DI)
DI47: LED46.1-DOUT (DO), LED47.3-DIN (DI)
DI48: LED47.1-DOUT (DO), LED48.3-DIN (DI)
DI49: LED48.1-DOUT (DO), LED49.3-DIN (DI)
DI50: LED49.1-DOUT (DO), LED50.3-DIN (DI)
DI51: LED50.1-DOUT (DO), LED51.3-DIN (DI)
DI52: LED51.1-DOUT (DO), LED52.3-DIN (DI)
DI53: LED52.1-DOUT (DO), LED53.3-DIN (DI)
DI54: LED53.1-DOUT (DO), LED54.3-DIN (DI)
DI55: LED54.1-DOUT (DO), LED55.3-DIN (DI)
DI56: LED55.1-DOUT (DO), LED56.3-DIN (DI)
DI57: LED56.1-DOUT (DO), LED57.3-DIN (DI)
DI58: LED57.1-DOUT (DO), LED58.3-DIN (DI)
DI59: LED58.1-DOUT (DO), LED59.3-DIN (DI)
DI60: LED59.1-DOUT (DO), LED60.3-DIN (DI)
DI61: LED60.1-DOUT (DO); also elsewhere on the board
GND: LED41.4-GND (GND), LED42.4-GND (GND), LED43.4-GND (GND), LED44.4-GND (GND), LED45.4-GND (GND), LED46.4-GND (GND), LED47.4-GND (GND), LED48.4-GND (GND), LED49.4-GND (GND), LED50.4-GND (GND), LED51.4-GND (GND), LED52.4-GND (GND), LED53.4-GND (GND), LED54.4-GND (GND), LED55.4-GND (GND), LED56.4-GND (GND), LED57.4-GND (GND), LED58.4-GND (GND), LED59.4-GND (GND), LED60.4-GND (GND); also elsewhere on the board
VDD: LED41.2-VDD (VDD), LED42.2-VDD (VDD), LED43.2-VDD (VDD), LED44.2-VDD (VDD), LED45.2-VDD (VDD), LED46.2-VDD (VDD), LED47.2-VDD (VDD), LED48.2-VDD (VDD), LED49.2-VDD (VDD), LED50.2-VDD (VDD), LED51.2-VDD (VDD), LED52.2-VDD (VDD), LED53.2-VDD (VDD), LED54.2-VDD (VDD), LED55.2-VDD (VDD), LED56.2-VDD (VDD), LED57.2-VDD (VDD), LED58.2-VDD (VDD), LED59.2-VDD (VDD), LED60.2-VDD (VDD); also elsewhere on the board
